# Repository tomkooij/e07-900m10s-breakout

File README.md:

# e07-900m10s-breakout

Breakout board for [ebyte e07-900m10s CC1101 module](https://www.ebyte.com/en/product-view-news.html?id=1567)

Breakout board vs well-known (but usually not working) CC1101 module for size:

Connected to waveshare ESP32 s3 mini (ramses_esp clone)

 - The header is a standard .1" (2.54mm) PCB header.
 - C1 and C2 are 1206 SMD size
 - C1 = 100nF
 - C2 = 10uF
 - C2 is probably not needed, it is used as a buffer for large currents while sending.
 - Antenna connector is [PCB SMA female](https://nl.aliexpress.com/item/1005005708712726.html) (use standard 1.6mm board thickness)
 - The IPEX stamp antenna on the module should also be useable (not tested)

This is my first KiCad/PCB. I'm happy it works!

This repo contains the KiCad 8 files as well as the gerbers to produce the PCB.
I used JLCPCB for my board. Just upload the zip-file in the gerber folder to JLCPCB.

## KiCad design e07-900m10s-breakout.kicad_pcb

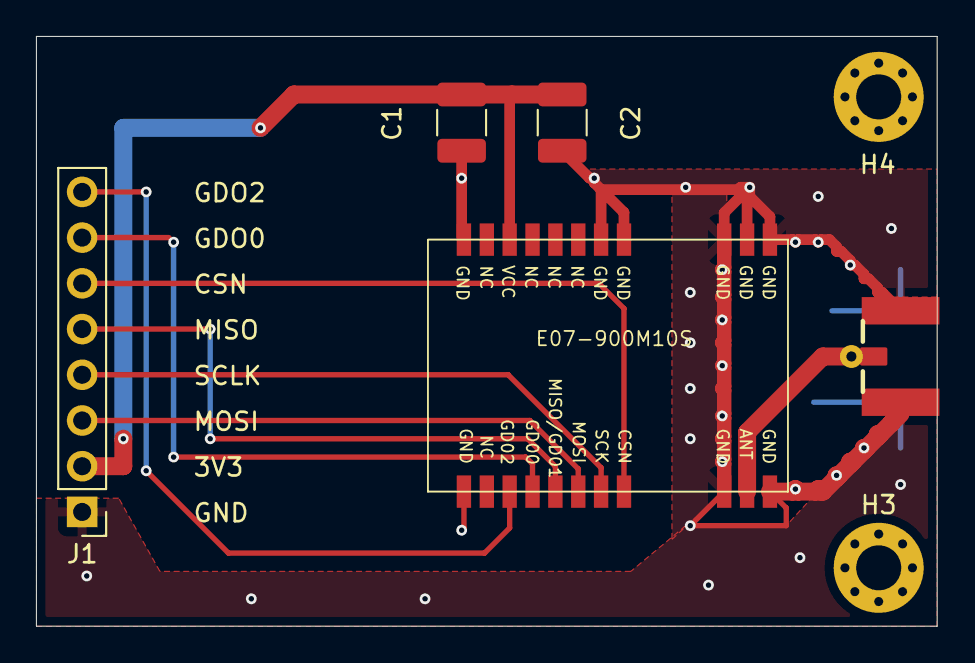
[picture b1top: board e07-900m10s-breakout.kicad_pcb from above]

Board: 2 copper layers, 50.0 x 32.8 mm, 7 parts (0 on the bottom side), 9 nets.

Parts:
C1: 100nF; C_1210_3225Metric_Pad1.33x2.70mm_HandSolder
C2: 4.7uF; C_1210_3225Metric_Pad1.33x2.70mm_HandSolder
H3, H4: MountingHole_Pad_MP; MountingHole_2.5mm_Pad_Via
J1: Conn_01x08_Pin; PinHeader_1x08_P2.54mm_Vertical
J$1: ANTENNASMA; SMA_PAD
U1: E07-900M10S

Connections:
3V3: C1.2, C2.2, J1.2, U1.9 (VCC)
/ANTENNA: J$1.ANT0 (ANT), J$1.ANT1 (ANT), J$1.ANT2 (ANT), U1.21 (ANT)
/CSN: J1.6, U1.19 (CSN)
/GDO0: J1.7, U1.15 (GDO0)
/GDO2: J1.8, U1.14 (GDO2)
/MISO: J1.5, U1.16 (GD01/MISO)
/MOSI: J1.3, U1.17 (MOSI)
/SCLK: J1.4, U1.18 (SCK)
GND: C1.1, C2.1, J1.1, J$1.GND3 (GND), J$1.GND4 (GND), J$1.GND5 (GND), J$1.GND6 (GND), U1.1 (GND), U1.2 (GND), U1.3 (GND), U1.4 (GND), U1.5 (GND), U1.11 (GND), U1.12 (GND), U1.20 (GND), U1.22 (GND)

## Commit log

2024-07-25 Initial commit of KiCad files + gerbers
2024-07-25 Add photos
2024-07-25 Add e07-900m10s manual
2024-07-26 Update README.md
    Board thickness is 1.6mm
2024-08-15 Update README.md
    C2 = 10uF
    jlCpcb not jlpcb
